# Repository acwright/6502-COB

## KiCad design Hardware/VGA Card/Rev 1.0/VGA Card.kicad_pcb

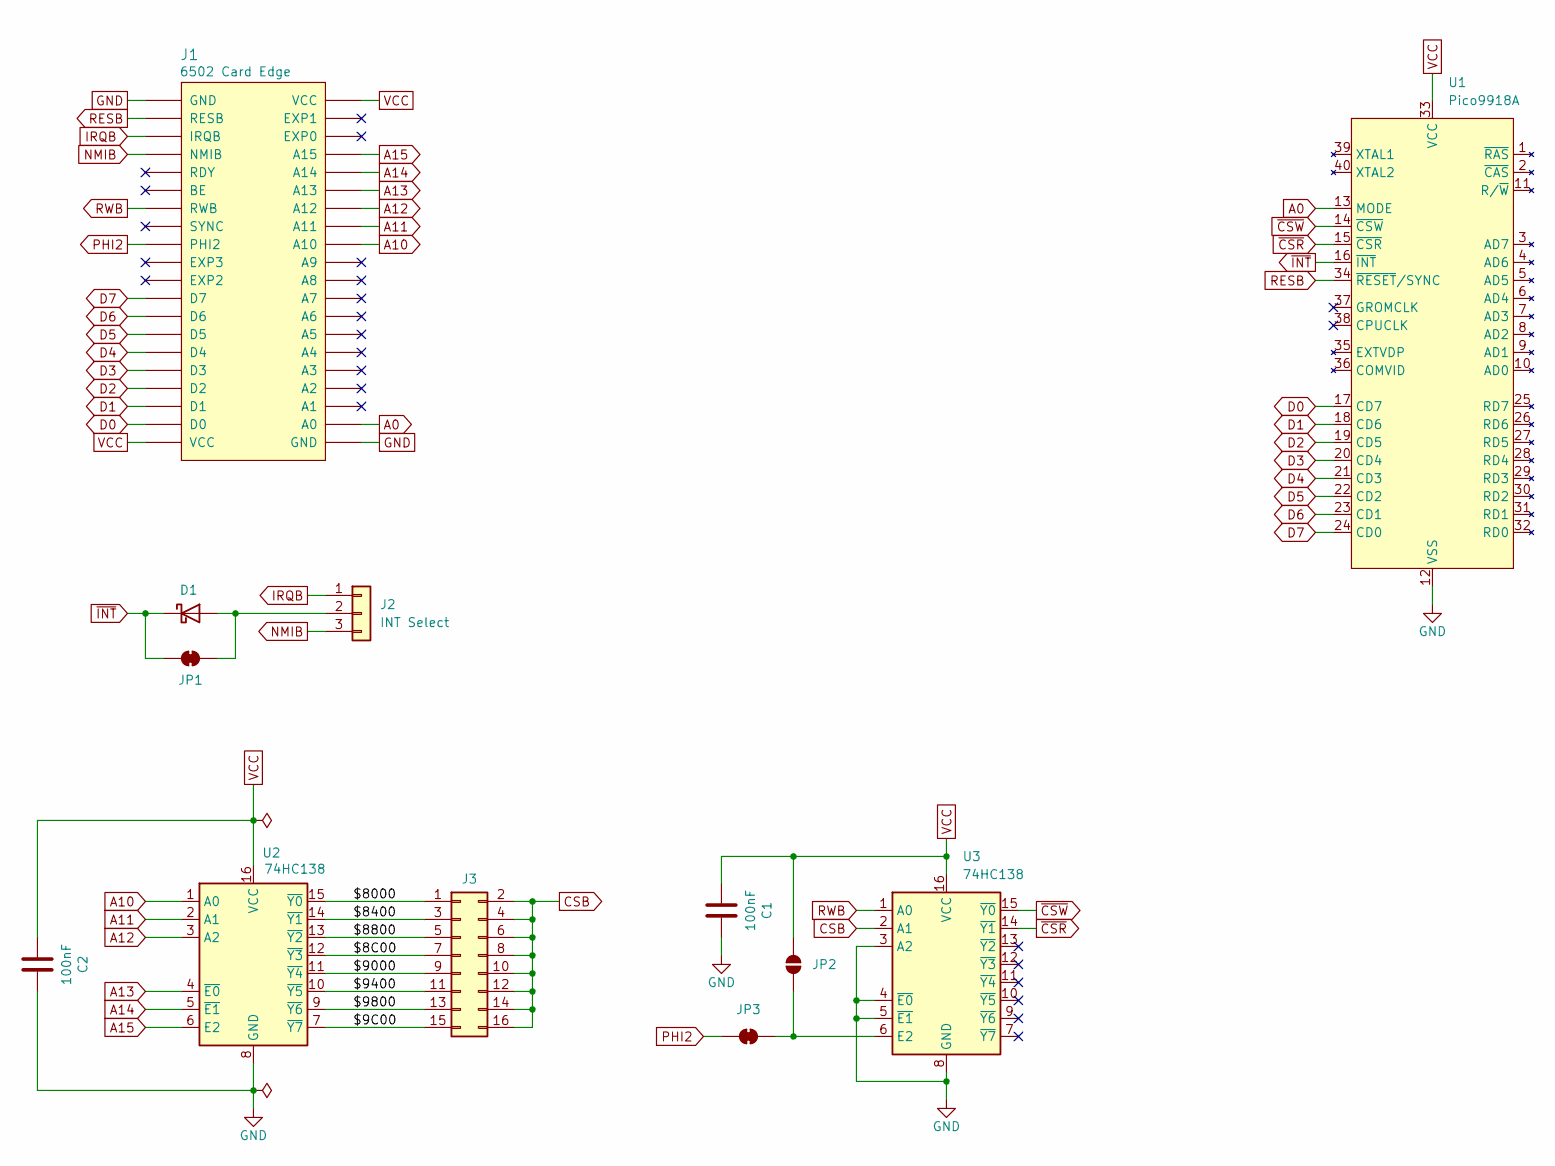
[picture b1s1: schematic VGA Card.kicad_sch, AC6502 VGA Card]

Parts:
C1, C2: 100nF; C_0805_2012Metric; LCSC C49678
D1: BAT85; D_DO-35_SOD27_P7.62mm_Horizontal; Digikey BAT85SCT-ND
J1: 6502 Card Edge
J2: INT Select; PinHeader_1x03_P2.54mm_Vertical; Digikey S1011EC-40-ND
J3: Conn_02x08_Odd_Even; PinHeader_2x08_P2.54mm_Vertical; Digikey S2011EC-40-ND
JP1, JP3: SolderJumper_2_Bridged; SolderJumper-2_P1.3mm_Bridged_RoundedPad1.0x1.5mm
JP2: SolderJumper_2_Open; SolderJumper-2_P1.3mm_Open_RoundedPad1.0x1.5mm
U1: Pico9918A; DIP-40_W15.24mm_LongPads
U2, U3: 74HC138; SOIC-16_3.9x9.9mm_P1.27mm; LCSC C5602

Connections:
/$8C00: J3.7, U2.12 (~Y3)
/$9C00: J3.15, U2.7 (~Y7)
/$8000: J3.1, U2.15 (~Y0)
/$8400: J3.3, U2.14 (~Y1)
/$8800: J3.5, U2.13 (~Y2)
/$9000: J3.9, U2.11 (~Y4)
/$9400: J3.11, U2.10 (~Y5)
/$9800: J3.13, U2.9 (~Y6)
A0: J1.A0, U1.13 (MODE)
A10: J1.A10, U2.1 (A0)
A11: J1.A11, U2.2 (A1)
A12: J1.A12, U2.3 (A2)
A13: J1.A13, U2.4 (~E0)
A14: J1.A14, U2.5 (~E1)
A15: J1.A15, U2.6 (E2)
CSB: J3.2, J3.4, J3.6, J3.8, J3.10, J3.12, J3.14, J3.16, U3.2 (A1)
D0: J1.D0, U1.17 (CD7)
D1: J1.D1, U1.18 (CD6)
D2: J1.D2, U1.19 (CD5)
D3: J1.D3, U1.20 (CD4)
D4: J1.D4, U1.21 (CD3)
D5: J1.D5, U1.22 (CD2)
D6: J1.D6, U1.23 (CD1)
D7: J1.D7, U1.24 (CD0)
GND: C1.2, C2.2, J1.GND, U1.12 (VSS), U2.8 (GND), U3.3 (A2), U3.4 (~E0), U3.5 (~E1), U3.8 (GND)
IRQB: J1.IRQB, J2.1
NMIB: J1.NMIB, J2.3
unnamed: D1.2 (A), J2.2, JP1.2 (B)
unnamed: JP2.2 (B), JP3.1 (A), U3.6 (E2)
PHI2: J1.PHI2, JP3.2 (B)
RESB: J1.RESB, U1.34 (~RESET/SYNC)
RWB: J1.RWB, U3.1 (A0)
VCC: C1.1, C2.1, J1.VCC, JP2.1 (A), U1.33 (VCC), U2.16 (VCC), U3.16 (VCC)
~CSR: U1.15 (~CSR), U3.14 (~Y1)
~CSW: U1.14 (~CSW), U3.15 (~Y0)
~INT: D1.1 (K), JP1.1 (A), U1.16 (~INT)

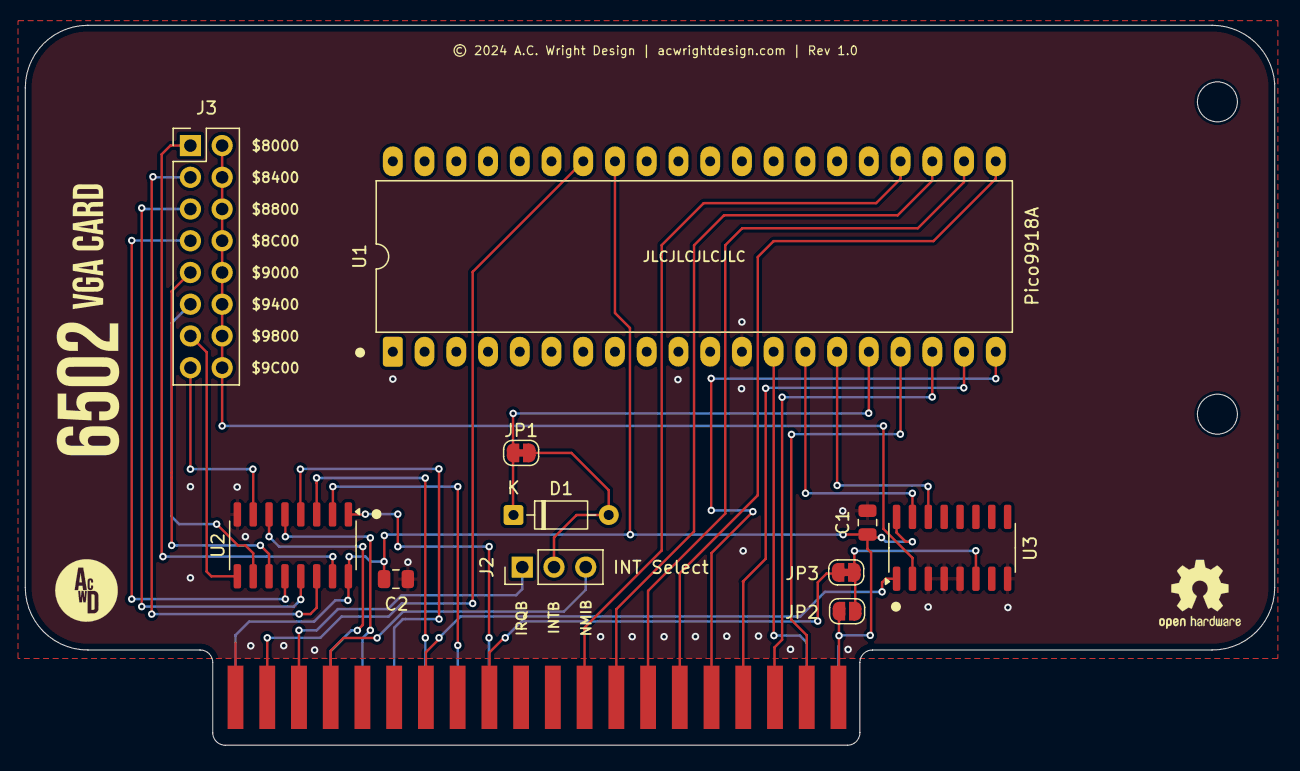
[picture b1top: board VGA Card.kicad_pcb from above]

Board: 2 copper layers, 100.0 x 57.6 mm, 12 parts (0 on the bottom side), 36 nets.

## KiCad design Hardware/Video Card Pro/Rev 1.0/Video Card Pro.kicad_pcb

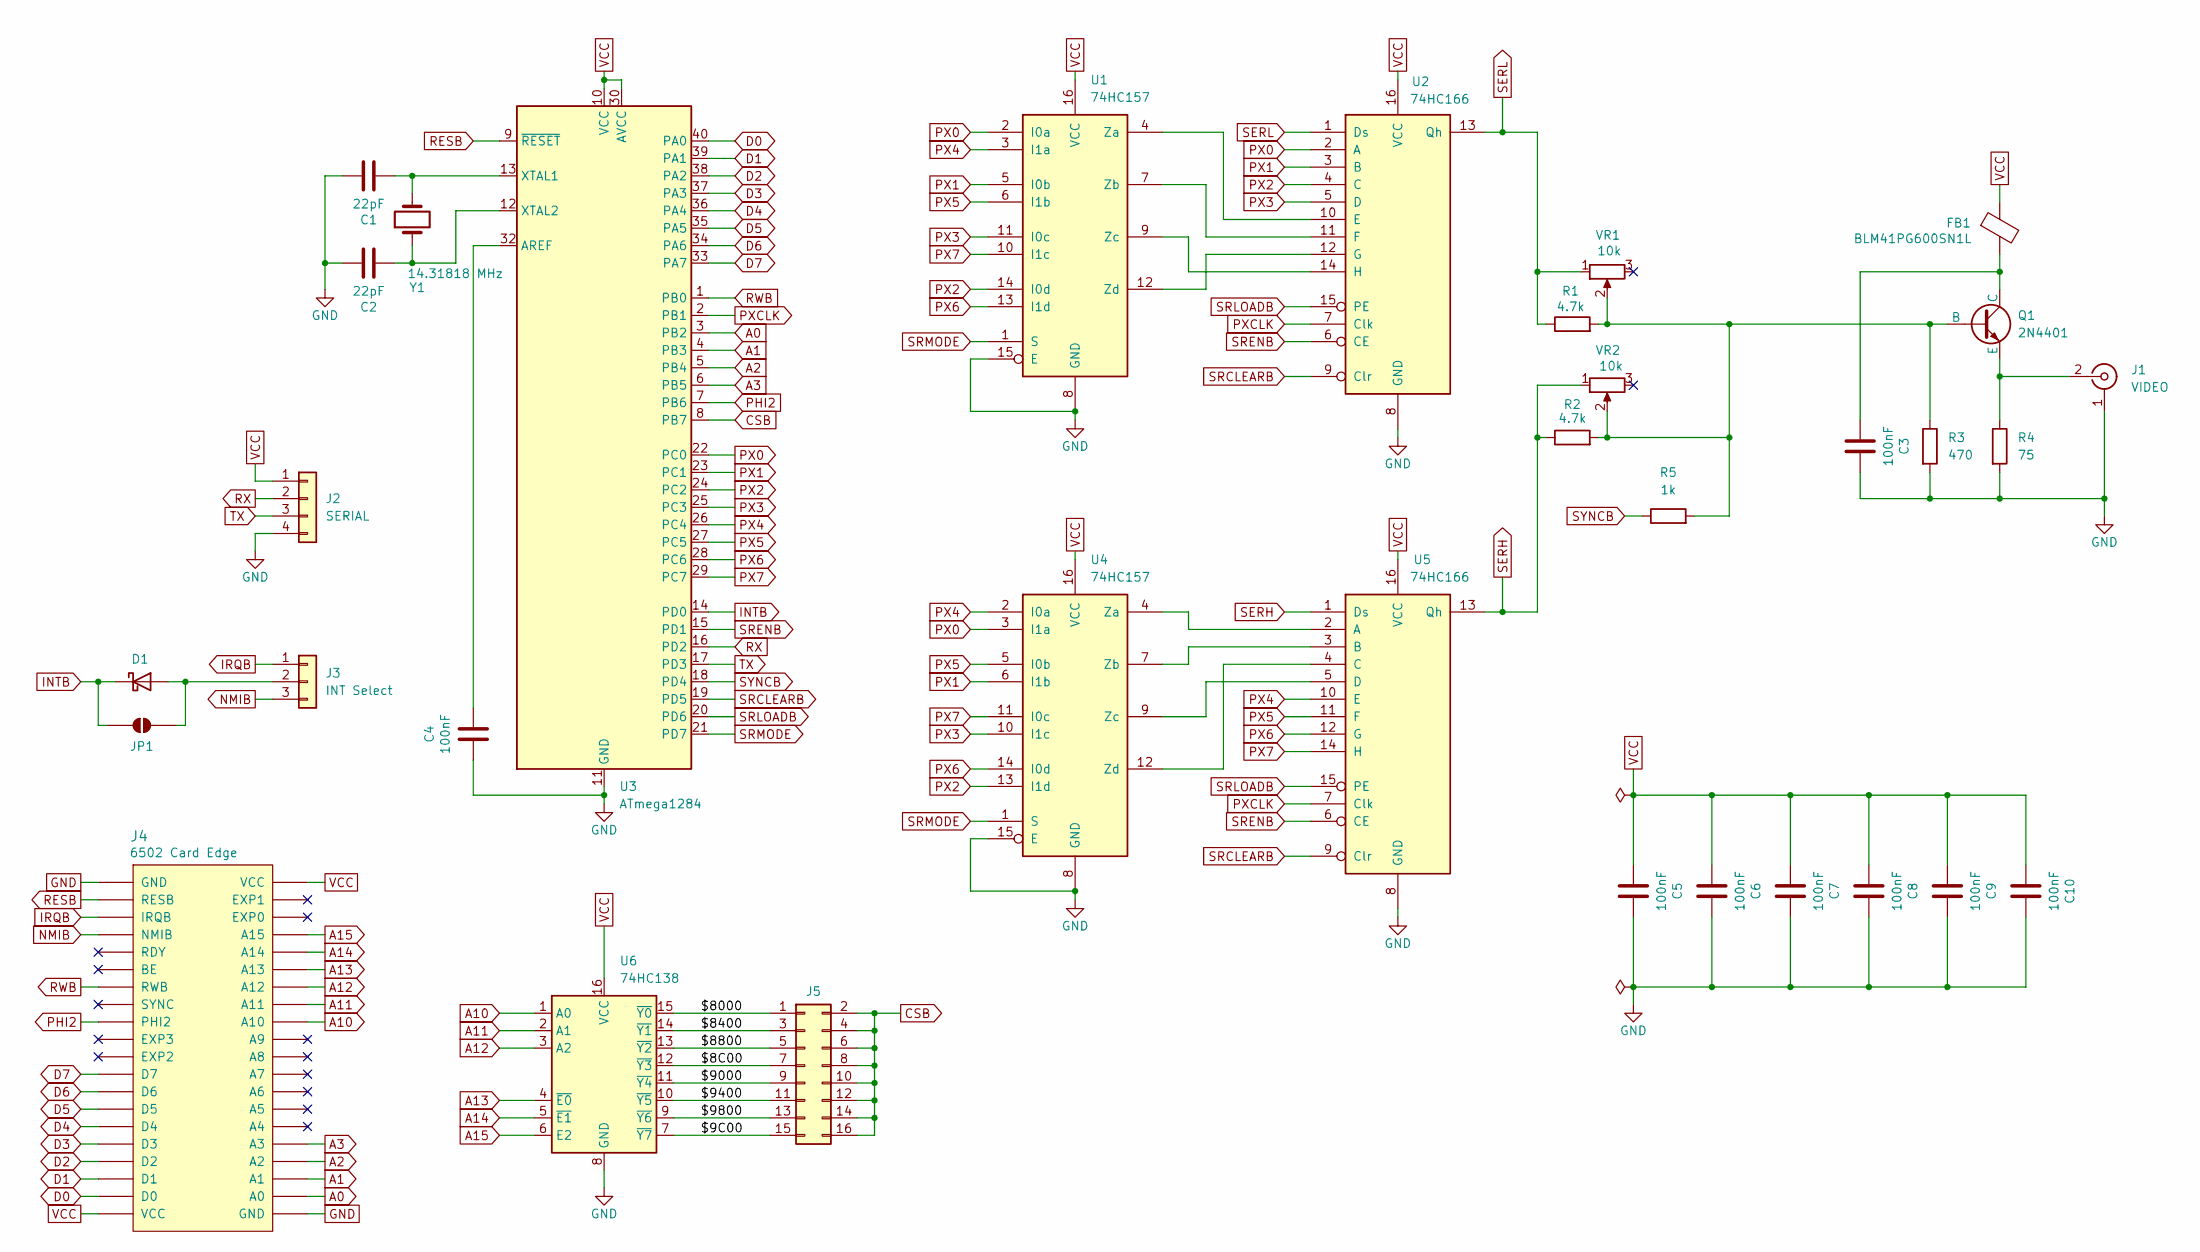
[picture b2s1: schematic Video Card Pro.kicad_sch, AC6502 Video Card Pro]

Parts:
C1, C2: 22pF; C_Disc_D5.0mm_W2.5mm_P2.50mm; Digikey 478-4846-ND
C3, C4, C5, C6, C7, C8, C9, C10: 100nF; C_0805_2012Metric; LCSC C49678
D1: BAT85; D_DO-35_SOD27_P7.62mm_Horizontal; Digikey BAT85SCT-ND
FB1: BLM41PG600SN1L; L_1806_4516Metric; LCSC C85844
J1: VIDEO; RCA Jack Yellow; Digikey PJRAN1X1U04X-ND
J2: SERIAL; PinHeader_1x04_P2.54mm_Vertical; Digikey S1011EC-40-ND
J3: INT Select; PinHeader_1x03_P2.54mm_Vertical; Digikey S1011EC-40-ND
J4: 6502 Card Edge
J5: Conn_02x08_Odd_Even; PinHeader_2x08_P2.54mm_Vertical; Digikey S2011EC-40-ND
JP1: SolderJumper_2_Open; SolderJumper-2_P1.3mm_Open_RoundedPad1.0x1.5mm
Q1: 2N4401; TO-92_HandSolder; Digikey 2N4401-ND
R1, R2: 4.7k; R_Axial_DIN0204_L3.6mm_D1.6mm_P5.08mm_Horizontal; Digikey 13-MFR-12FTF52-4K7CT-ND
R3: 470; R_0805_2012Metric; LCSC C17710
R4: 75; R_0805_2012Metric; LCSC C17820
R5: 1k; R_Axial_DIN0204_L3.6mm_D1.6mm_P5.08mm_Horizontal; Digikey 13-MFR-12FTF52-1KCT-ND
U1, U4: 74HC157; SOIC-16_3.9x9.9mm_P1.27mm; LCSC C6823
U2, U5: 74HC166; SOIC-16_3.9x9.9mm_P1.27mm; LCSC C473363
U3: ATmega1284; DIP-40_W15.24mm_Socket_LongPads; Digikey ATMEGA1284-PU-ND
U6: 74HC138; SOIC-16_3.9x9.9mm_P1.27mm; LCSC C5602
VR1, VR2: 10k; Trimmer 3386F; Digikey 3386F-103LF-ND
Y1: 14.31818 MHz; Crystal_HC49-U_Vertical; Mouser 520-HCU143-20-4X

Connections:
/$8C00: J5.7, U6.12 (~Y3)
/$9C00: J5.15, U6.7 (~Y7)
/$8000: J5.1, U6.15 (~Y0)
/$8400: J5.3, U6.14 (~Y1)
/$8800: J5.5, U6.13 (~Y2)
/$9000: J5.9, U6.11 (~Y4)
/$9400: J5.11, U6.10 (~Y5)
/$9800: J5.13, U6.9 (~Y6)
A0: J4.A0, U3.3 (PB2)
A1: J4.A1, U3.4 (PB3)
A2: J4.A2, U3.5 (PB4)
A3: J4.A3, U3.6 (PB5)
A10: J4.A10, U6.1 (A0)
A11: J4.A11, U6.2 (A1)
A12: J4.A12, U6.3 (A2)
A13: J4.A13, U6.4 (~E0)
A14: J4.A14, U6.5 (~E1)
A15: J4.A15, U6.6 (E2)
CSB: J5.2, J5.4, J5.6, J5.8, J5.10, J5.12, J5.14, J5.16, U3.8 (PB7)
D0: J4.D0, U3.40 (PA0)
D1: J4.D1, U3.39 (PA1)
D2: J4.D2, U3.38 (PA2)
D3: J4.D3, U3.37 (PA3)
D4: J4.D4, U3.36 (PA4)
D5: J4.D5, U3.35 (PA5)
D6: J4.D6, U3.34 (PA6)
D7: J4.D7, U3.33 (PA7)
GND: C1.2, C2.2, C3.2, C4.1, C5.2, C6.2, C7.2, C8.2, C9.2, C10.2, J1.1 (Ext), J2.4, J4.GND, R3.2, R4.2, U1.8 (GND), U1.15 (E), U2.8 (GND), U3.11 (GND), U3.31 (GND), U4.8 (GND), U4.15 (E), U5.8 (GND), U6.8 (GND)
INTB: D1.1 (K), JP1.1 (A), U3.14 (PD0)
IRQB: J3.1, J4.IRQB
NMIB: J3.3, J4.NMIB
unnamed: D1.2 (A), J3.2, JP1.2 (B)
unnamed: J1.2 (In), Q1.3 (E), R4.1
unnamed: Q1.2 (B), R1.2, R2.2, R3.1, R5.2, VR1.2, VR2.2
unnamed: C3.1, FB1.2, Q1.1 (C)
unnamed: U1.4 (Za), U2.10 (E)
unnamed: U1.7 (Zb), U2.11 (F)
unnamed: U1.9 (Zc), U2.14 (H)
unnamed: U1.12 (Zd), U2.12 (G)
unnamed: C4.2, U3.32 (AREF)
unnamed: C1.1, U3.13 (XTAL1), Y1.2
unnamed: C2.1, U3.12 (XTAL2), Y1.1
unnamed: U4.4 (Za), U5.2 (A)
unnamed: U4.7 (Zb), U5.3 (B)
unnamed: U4.9 (Zc), U5.5 (D)
unnamed: U4.12 (Zd), U5.4 (C)
PHI2: J4.PHI2, U3.7 (PB6)
PX0: U1.2 (I0a), U2.2 (A), U3.22 (PC0), U4.3 (I1a)
PX1: U1.5 (I0b), U2.3 (B), U3.23 (PC1), U4.6 (I1b)
PX2: U1.14 (I0d), U2.4 (C), U3.24 (PC2), U4.13 (I1d)
PX3: U1.11 (I0c), U2.5 (D), U3.25 (PC3), U4.10 (I1c)
PX4: U1.3 (I1a), U3.26 (PC4), U4.2 (I0a), U5.10 (E)
PX5: U1.6 (I1b), U3.27 (PC5), U4.5 (I0b), U5.11 (F)
PX6: U1.13 (I1d), U3.28 (PC6), U4.14 (I0d), U5.12 (G)
PX7: U1.10 (I1c), U3.29 (PC7), U4.11 (I0c), U5.14 (H)
PXCLK: U2.7 (Clk), U3.2 (PB1), U5.7 (Clk)
RESB: J4.RESB, U3.9 (~RESET)
RWB: J4.RWB, U3.1 (PB0)
RX: J2.2, U3.16 (PD2)
SERH: R2.1, U5.1 (Ds), U5.13 (Qh), VR2.1
SERL: R1.1, U2.1 (Ds), U2.13 (Qh), VR1.1
SRCLEARB: U2.9 (Clr), U3.19 (PD5), U5.9 (Clr)
SRENB: U2.6 (CE), U3.15 (PD1), U5.6 (CE)
SRLOADB: U2.15 (PE), U3.20 (PD6), U5.15 (PE)
SRMODE: U1.1 (S), U3.21 (PD7), U4.1 (S)
SYNCB: R5.1, U3.18 (PD4)
TX: J2.3, U3.17 (PD3)
VCC: C5.1, C6.1, C7.1, C8.1, C9.1, C10.1, FB1.1, J2.1, J4.VCC, U1.16 (VCC), U2.16 (VCC), U3.10 (VCC), U3.30 (AVCC), U4.16 (VCC), U5.16 (VCC), U6.16 (VCC)

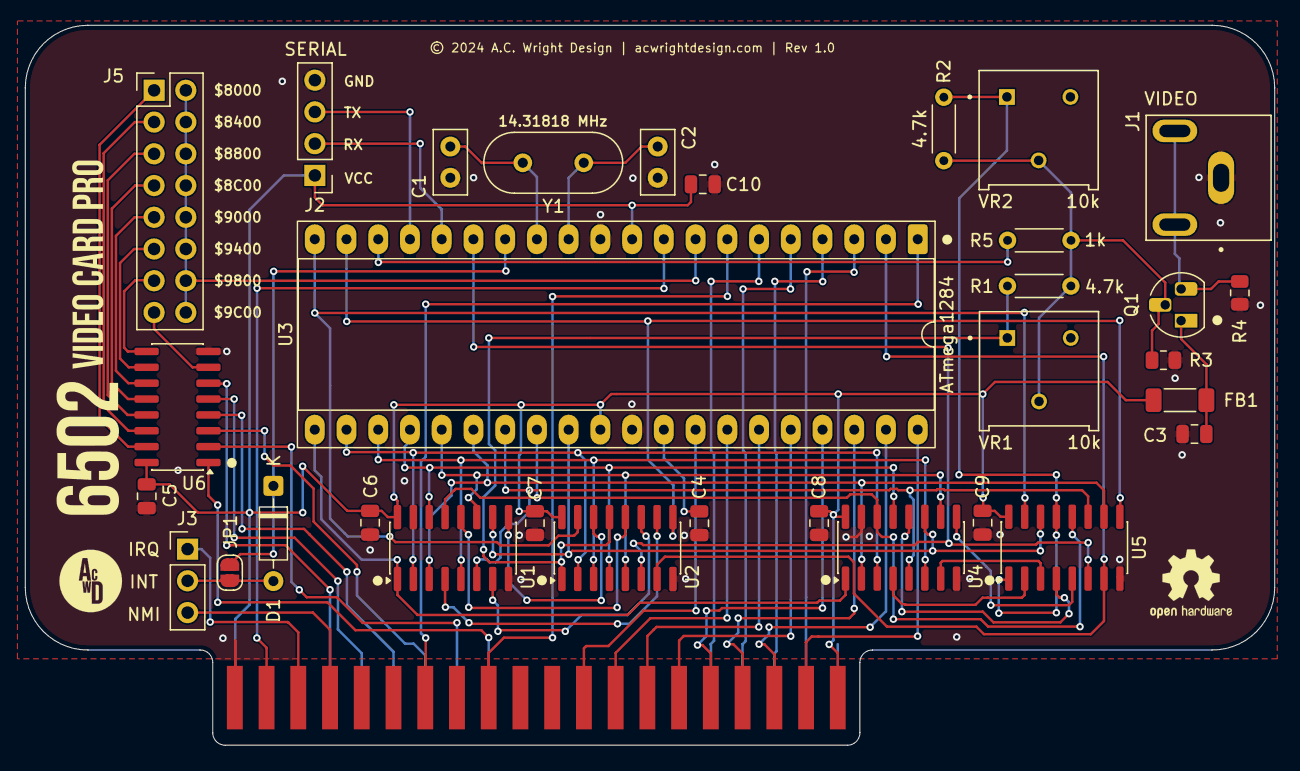
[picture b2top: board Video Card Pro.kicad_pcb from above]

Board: 2 copper layers, 100.0 x 57.6 mm, 33 parts (0 on the bottom side), 68 nets.

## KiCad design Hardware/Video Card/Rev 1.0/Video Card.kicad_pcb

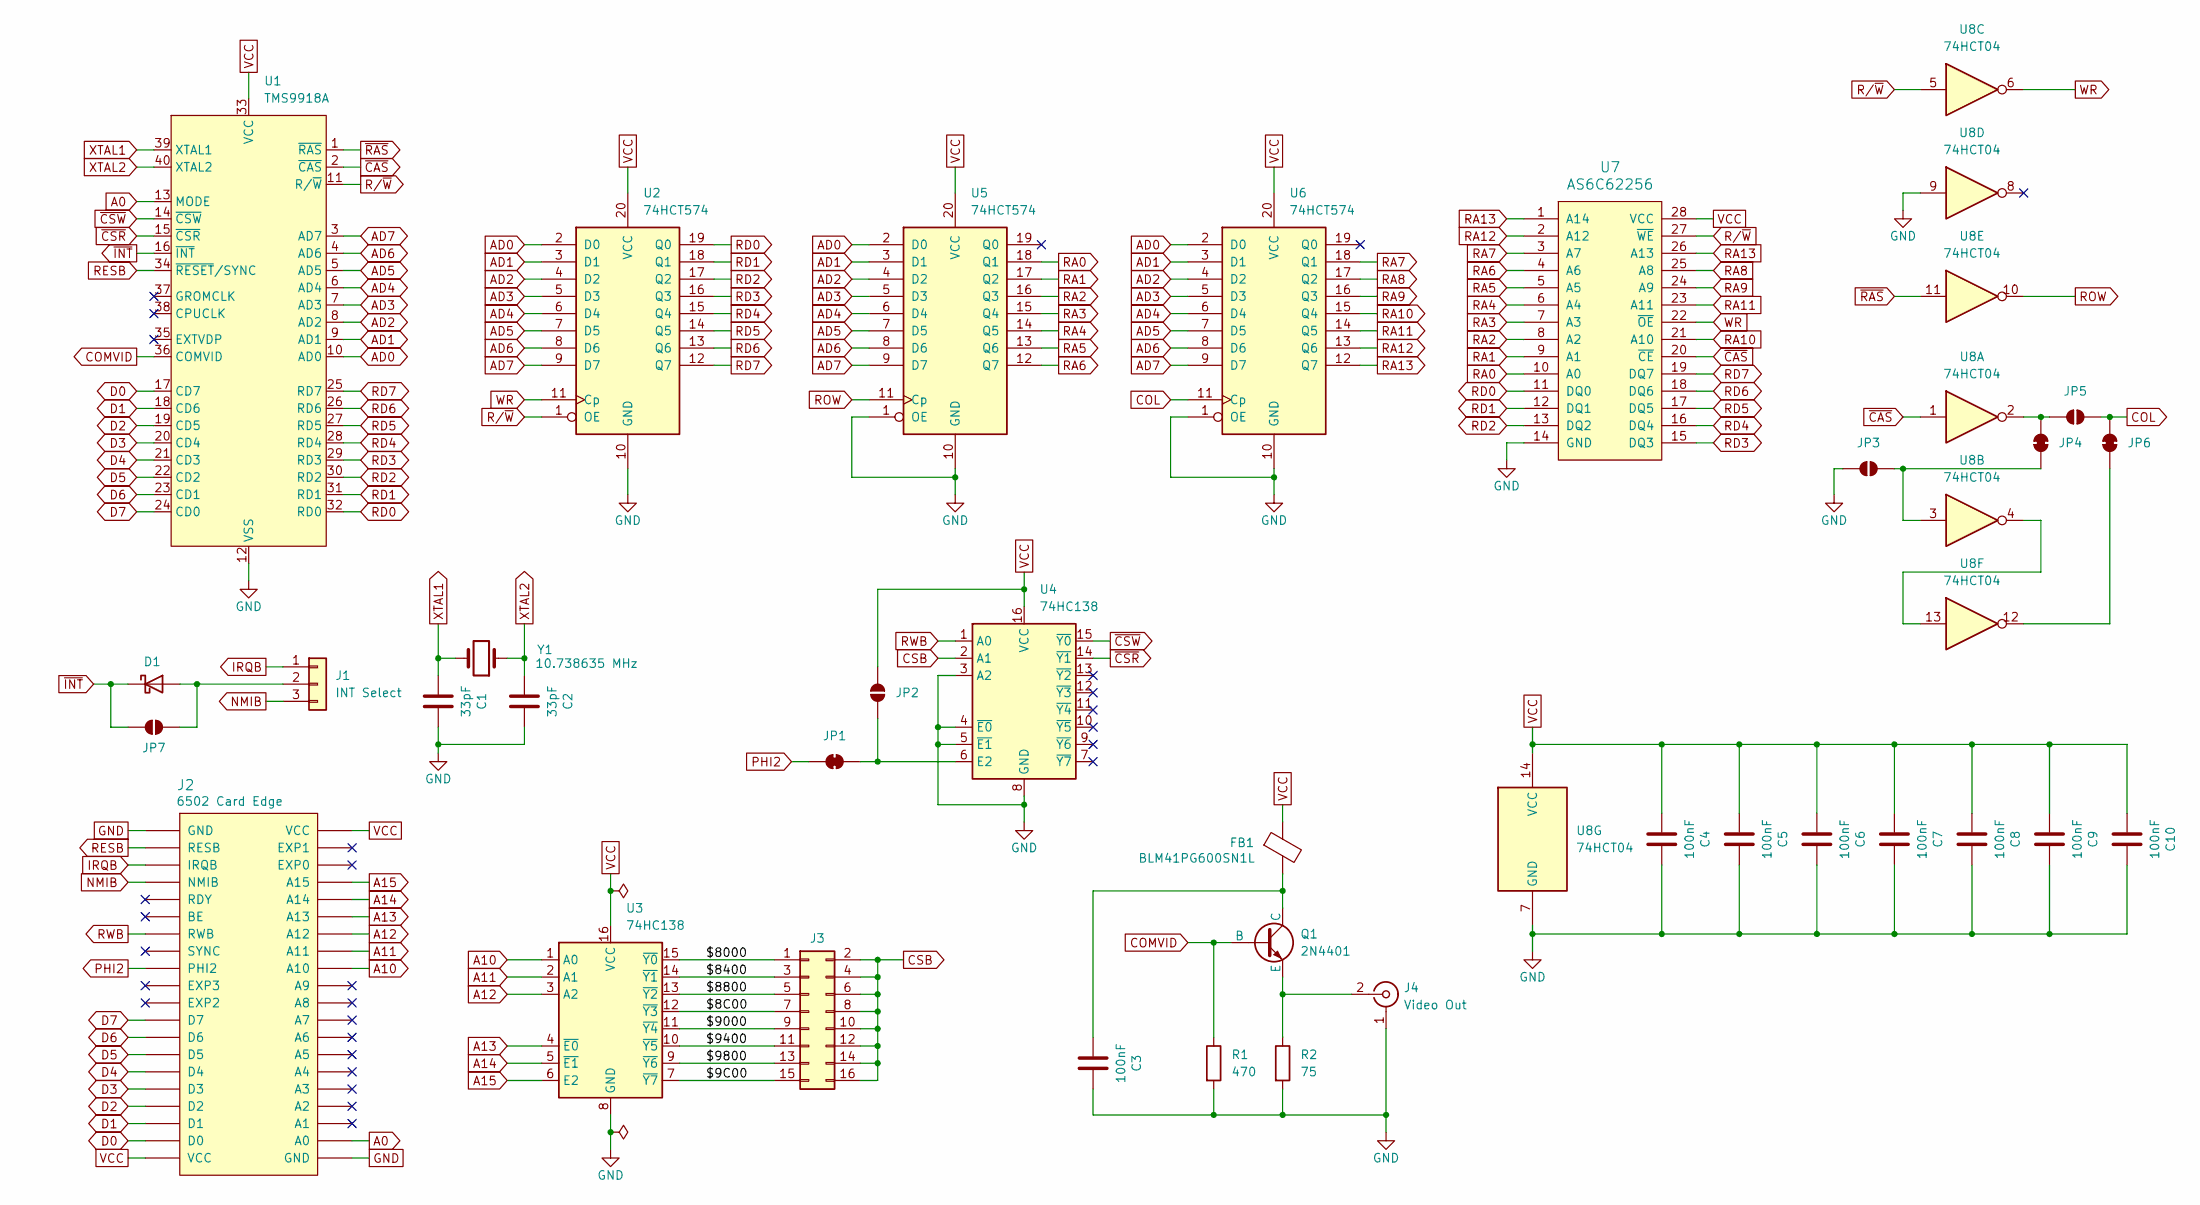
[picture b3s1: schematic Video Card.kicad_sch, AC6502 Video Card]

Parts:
C1, C2: 33pF; C_Disc_D5.0mm_W2.5mm_P2.50mm; Digikey 478-4849-ND
C3, C4, C5, C6, C7, C8, C9, C10: 100nF; C_0805_2012Metric; LCSC C49678
D1: BAT85; D_DO-35_SOD27_P7.62mm_Horizontal; Digikey BAT85SCT-ND
FB1: BLM41PG600SN1L; L_1806_4516Metric; LCSC C85844
J1: INT Select; PinHeader_1x03_P2.54mm_Vertical; Digikey S1011EC-40-ND
J2: 6502 Card Edge
J3: Conn_02x08_Odd_Even; PinHeader_2x08_P2.54mm_Vertical; Digikey S2011EC-40-ND
J4: Video Out; RCA Jack Yellow; Digikey PJRAN1X1U04X-ND
JP1, JP4, JP6: SolderJumper_2_Bridged; SolderJumper-2_P1.3mm_Bridged_RoundedPad1.0x1.5mm
JP2, JP3, JP5: SolderJumper_2_Open; SolderJumper-2_P1.3mm_Open_RoundedPad1.0x1.5mm
JP7: SolderJumper_2_Bridged; SolderJumper-2_P1.3mm_Open_RoundedPad1.0x1.5mm
Q1: 2N4401; TO-92_HandSolder; Digikey 2N4401-ND
R1: 470; R_0805_2012Metric; LCSC C17710
R2: 75; R_0805_2012Metric; LCSC C17820
U1: TMS9918A; DIP-40_W15.24mm_LongPads
U2, U5, U6: 74HCT574; SOIC-20W_7.5x12.8mm_P1.27mm; LCSC C6001
U3, U4: 74HC138; SOIC-16_3.9x9.9mm_P1.27mm; LCSC C5602
U7: AS6C62256; DIP-28_W15.24mm_LongPads; Digikey 1450-1033-ND
U8: 74HCT04; SO-14_3.9x8.65mm_P1.27mm; LCSC C672096
Y1: 10.738635 MHz; Crystal_HC49-U_Vertical; Mouser 774-MP107-E

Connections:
/$8C00: J3.7, U3.12 (~Y3)
/$9C00: J3.15, U3.7 (~Y7)
/$8000: J3.1, U3.15 (~Y0)
/$8400: J3.3, U3.14 (~Y1)
/$8800: J3.5, U3.13 (~Y2)
/$9000: J3.9, U3.11 (~Y4)
/$9400: J3.11, U3.10 (~Y5)
/$9800: J3.13, U3.9 (~Y6)
A0: J2.A0, U1.13 (MODE)
A10: J2.A10, U3.1 (A0)
A11: J2.A11, U3.2 (A1)
A12: J2.A12, U3.3 (A2)
A13: J2.A13, U3.4 (~E0)
A14: J2.A14, U3.5 (~E1)
A15: J2.A15, U3.6 (E2)
AD0: U1.10 (AD0), U2.2 (D0), U5.2 (D0), U6.2 (D0)
AD1: U1.9 (AD1), U2.3 (D1), U5.3 (D1), U6.3 (D1)
AD2: U1.8 (AD2), U2.4 (D2), U5.4 (D2), U6.4 (D2)
AD3: U1.7 (AD3), U2.5 (D3), U5.5 (D3), U6.5 (D3)
AD4: U1.6 (AD4), U2.6 (D4), U5.6 (D4), U6.6 (D4)
AD5: U1.5 (AD5), U2.7 (D5), U5.7 (D5), U6.7 (D5)
AD6: U1.4 (AD6), U2.8 (D6), U5.8 (D6), U6.8 (D6)
AD7: U1.3 (AD7), U2.9 (D7), U5.9 (D7), U6.9 (D7)
COL: JP5.1 (A), JP6.2 (B), U6.11 (Cp)
COMVID: Q1.2 (B), R1.1, U1.36 (COMVID)
CSB: J3.2, J3.4, J3.6, J3.8, J3.10, J3.12, J3.14, J3.16, U4.2 (A1)
D0: J2.D0, U1.17 (CD7)
D1: J2.D1, U1.18 (CD6)
D2: J2.D2, U1.19 (CD5)
D3: J2.D3, U1.20 (CD4)
D4: J2.D4, U1.21 (CD3)
D5: J2.D5, U1.22 (CD2)
D6: J2.D6, U1.23 (CD1)
D7: J2.D7, U1.24 (CD0)
GND: C1.2, C2.2, C3.2, C4.2, C5.2, C6.2, C7.2, C8.2, C9.2, C10.2, J2.GND, J4.1 (Ext), JP3.2 (B), R1.2, R2.2, U1.12 (VSS), U2.10 (GND), U3.8 (GND), U4.3 (A2), U4.4 (~E0), U4.5 (~E1), U4.8 (GND), U5.1 (OE), U5.10 (GND), U6.1 (OE), U6.10 (GND), U7.14 (GND), U8.7 (GND), U8.9
IRQB: J1.1, J2.IRQB
NMIB: J1.3, J2.NMIB
unnamed: D1.2 (A), J1.2, JP7.2 (B)
unnamed: J4.2 (In), Q1.3 (E), R2.1
unnamed: JP1.1 (A), JP2.2 (B), U4.6 (E2)
unnamed: JP3.1 (A), JP4.1 (A), U8.3
unnamed: JP4.2 (B), JP5.2 (B), U8.2
unnamed: JP6.1 (A), U8.12
unnamed: C3.1, FB1.2, Q1.1 (C)
unnamed: U8.4, U8.13
PHI2: J2.PHI2, JP1.2 (B)
RA0: U5.18 (Q1), U7.10 (A0)
RA1: U5.17 (Q2), U7.9 (A1)
RA2: U5.16 (Q3), U7.8 (A2)
RA3: U5.15 (Q4), U7.7 (A3)
RA4: U5.14 (Q5), U7.6 (A4)
RA5: U5.13 (Q6), U7.5 (A5)
RA6: U5.12 (Q7), U7.4 (A6)
RA7: U6.18 (Q1), U7.3 (A7)
RA8: U6.17 (Q2), U7.25 (A8)
RA9: U6.16 (Q3), U7.24 (A9)
RA10: U6.15 (Q4), U7.21 (A10)
RA11: U6.14 (Q5), U7.23 (A11)
RA12: U6.13 (Q6), U7.2 (A12)
RA13: U6.12 (Q7), U7.1 (A14), U7.26 (A13)
RD0: U1.32 (RD0), U2.19 (Q0), U7.11 (DQ0)
RD1: U1.31 (RD1), U2.18 (Q1), U7.12 (DQ1)
RD2: U1.30 (RD2), U2.17 (Q2), U7.13 (DQ2)
RD3: U1.29 (RD3), U2.16 (Q3), U7.15 (DQ3)
RD4: U1.28 (RD4), U2.15 (Q4), U7.16 (DQ4)
RD5: U1.27 (RD5), U2.14 (Q5), U7.17 (DQ5)
RD6: U1.26 (RD6), U2.13 (Q6), U7.18 (DQ6)
RD7: U1.25 (RD7), U2.12 (Q7), U7.19 (DQ7)
RESB: J2.RESB, U1.34 (~RESET/SYNC)
ROW: U5.11 (Cp), U8.10
RWB: J2.RWB, U4.1 (A0)
R/~W: U1.11 (R/~W), U2.1 (OE), U7.27 (~WE), U8.5
VCC: C4.1, C5.1, C6.1, C7.1, C8.1, C9.1, C10.1, FB1.1, J2.VCC, JP2.1 (A), U1.33 (VCC), U2.20 (VCC), U3.16 (VCC), U4.16 (VCC), U5.20 (VCC), U6.20 (VCC), U7.28 (VCC), U8.14 (VCC)
WR: U2.11 (Cp), U7.22 (~OE), U8.6
XTAL1: C1.1, U1.39 (XTAL1), Y1.2
XTAL2: C2.1, U1.40 (XTAL2), Y1.1
~CAS: U1.2 (~CAS), U7.20 (~CE), U8.1
~CSR: U1.15 (~CSR), U4.14 (~Y1)
~CSW: U1.14 (~CSW), U4.15 (~Y0)
~INT: D1.1 (K), JP7.1 (A), U1.16 (~INT)
~RAS: U1.1 (~RAS), U8.11

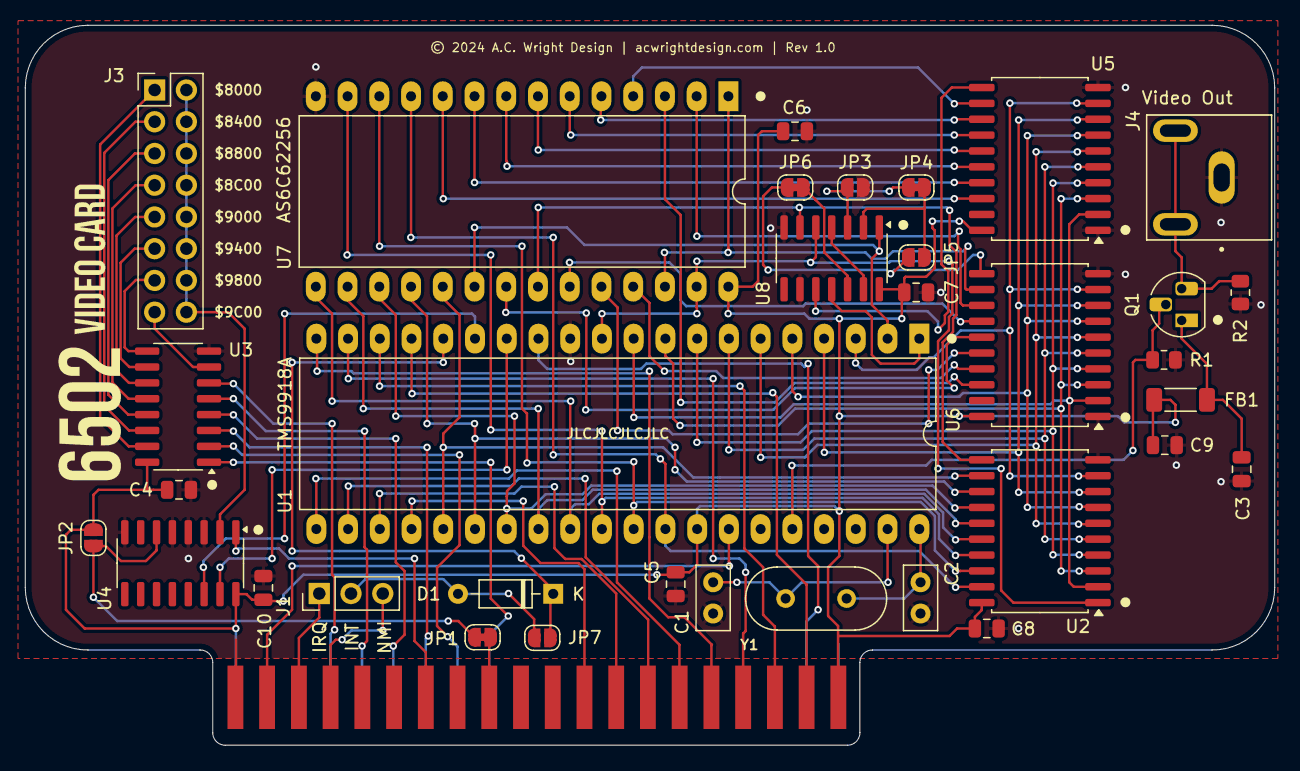
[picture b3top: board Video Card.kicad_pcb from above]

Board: 2 copper layers, 100.0 x 57.6 mm, 35 parts (0 on the bottom side), 81 nets.

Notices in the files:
Hardware/VGA Card/Rev 1.0/VGA Card.kicad_pcb:
© 2024 A.C. Wright Design | acwrightdesign.com | Rev 1.0
